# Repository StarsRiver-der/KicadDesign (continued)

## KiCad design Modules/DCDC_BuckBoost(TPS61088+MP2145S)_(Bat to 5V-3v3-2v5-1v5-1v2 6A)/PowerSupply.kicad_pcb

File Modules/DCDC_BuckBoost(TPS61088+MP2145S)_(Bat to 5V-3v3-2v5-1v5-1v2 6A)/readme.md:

# 2.8V-4.2V 锂电池输入的 DCDC 单极性多轨电源
* 工作温度：0-85℃
* 5V、3v3、2v5、1v5、1v2多轨输出
* 最高30W输出

# 注意事项
* 使用Kicad6绘制

# 原理
见说明手册

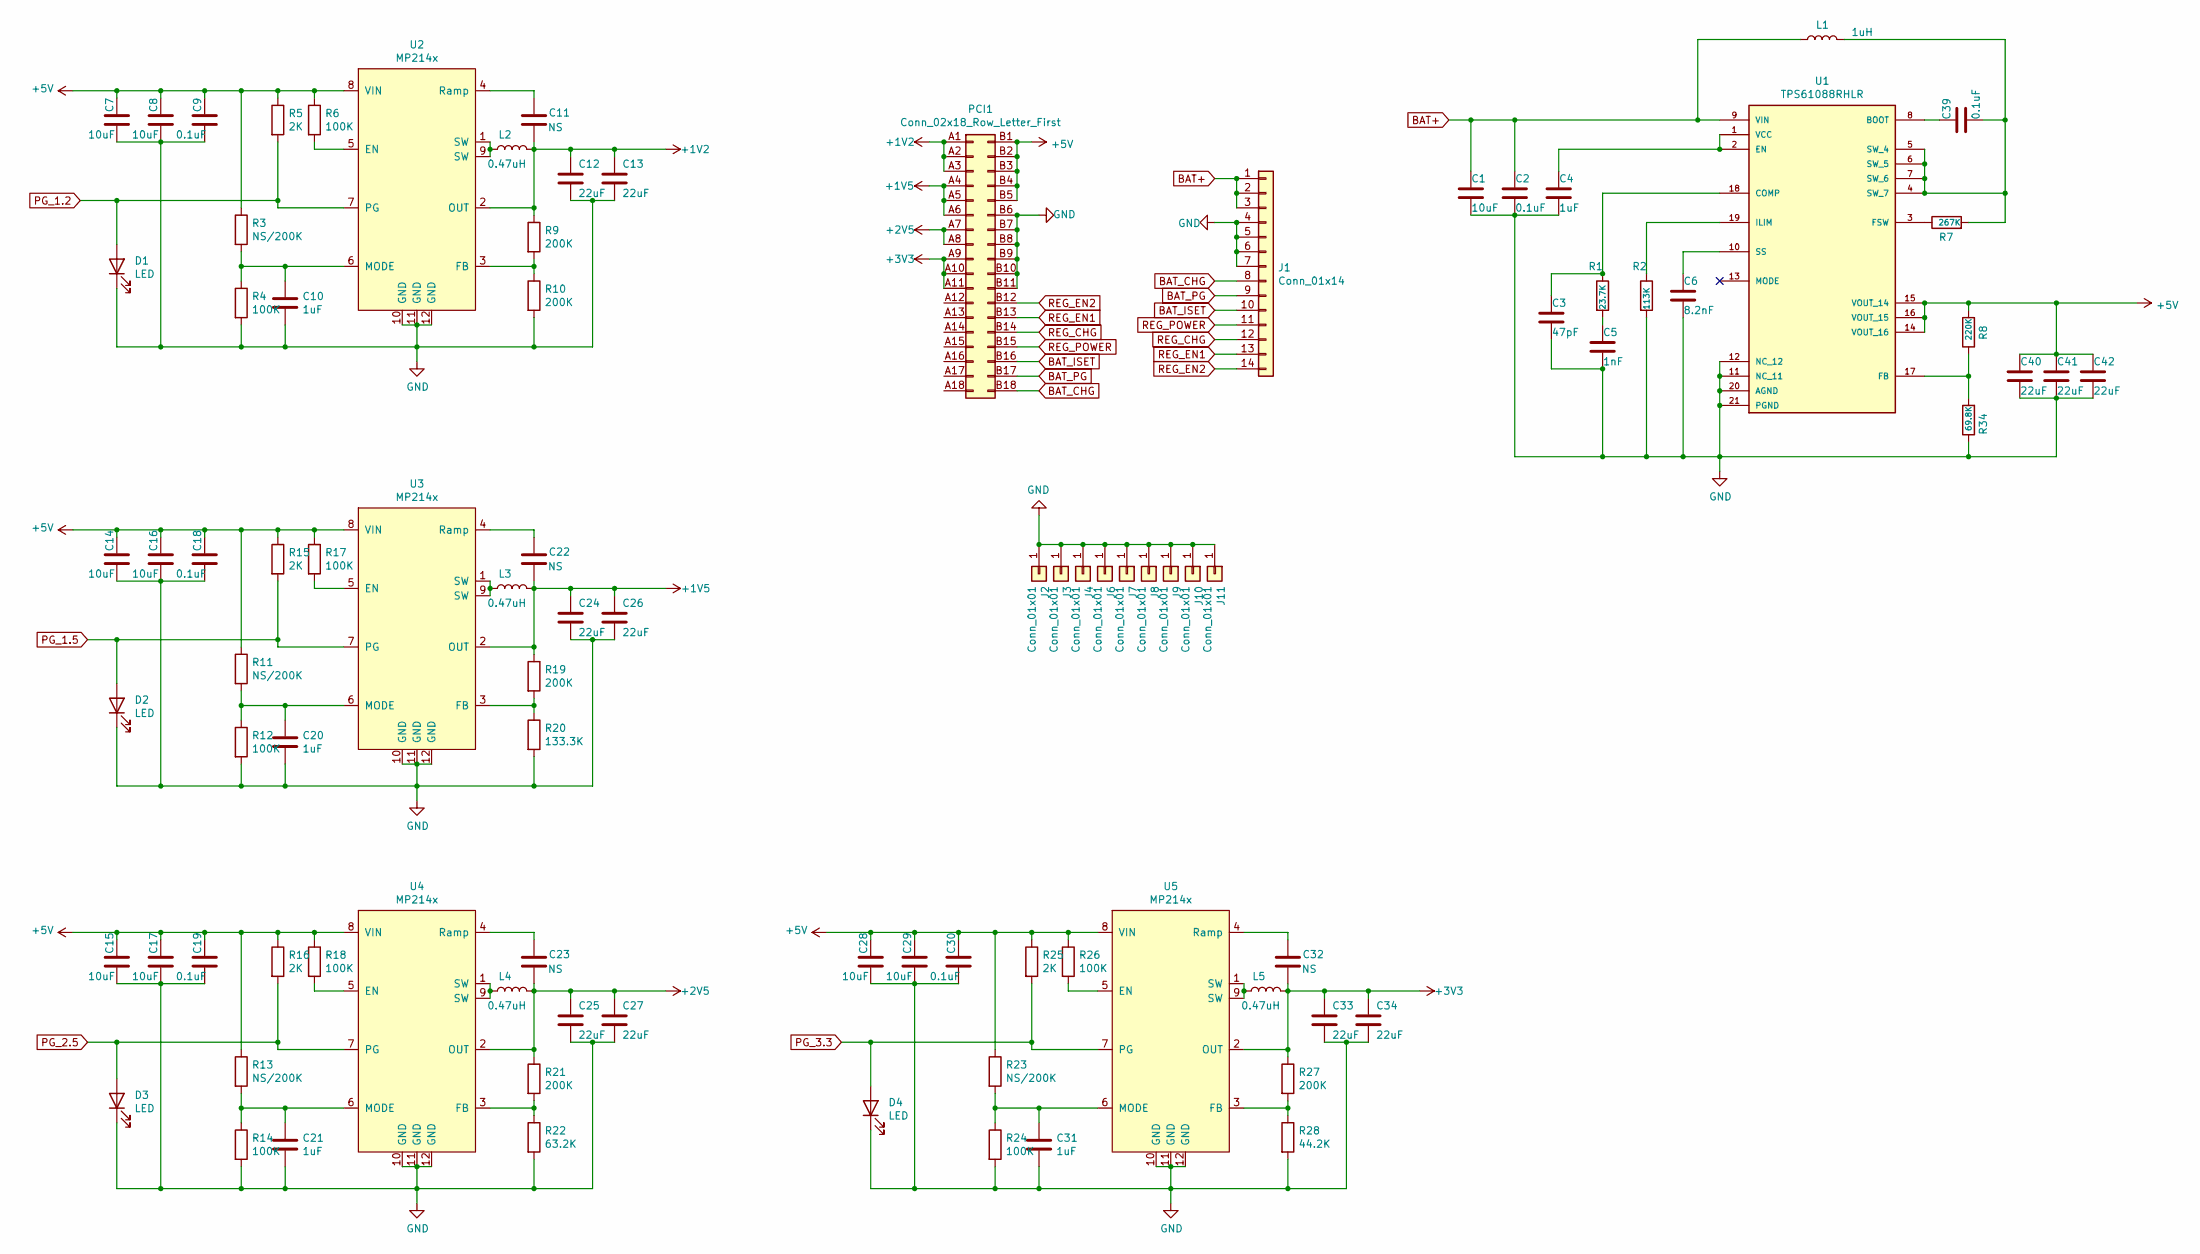
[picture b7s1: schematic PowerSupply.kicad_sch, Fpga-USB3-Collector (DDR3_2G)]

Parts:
C1, C7, C8, C14, C15, C16, C17, C28, C29: 10uF; C_0603_1608Metric
C2, C9, C18, C19, C30, C39: 0.1uF; C_0402_1005Metric
C3: 47pF; C_0402_1005Metric
C4, C10, C20, C21, C31: 1uF; C_0402_1005Metric
C5: 1nF; C_0402_1005Metric
C6: 8.2nF; C_0402_1005Metric
C11, C22, C23, C32: NS; C_0402_1005Metric
C12, C13, C24, C25, C26, C27, C33, C34, C40, C41, C42: 22uF; C_0603_1608Metric
D1, D2, D3, D4: LED; LED_0402_1005Metric
J1: Conn_01x14; Hirose_FH12-14S-0.5SH_1x14-1MP_P0.50mm_Horizontal
J2, J3, J4, J6, J7, J8, J9, J10, J11: Conn_01x01; pad-6-1.5
L1: 1uH; L_Sunlord_MWSA0518_5.4x5.2mm
L2, L3, L4, L5: 0.47uH; L_Sunlord_MWSA0518_5.4x5.2mm
PCI1: Conn_02x18_Row_Letter_First; BUS_PCIexpress_x1
R1: 23.7K; R_0402_1005Metric
R2: 113K; R_0402_1005Metric
R3, R11, R13, R23: NS/200K; R_0402_1005Metric
R4, R6, R12, R14, R17, R18, R24, R26: 100K; R_0402_1005Metric
R5, R15, R16, R25: 2K; R_0402_1005Metric
R7: 267K; R_0402_1005Metric
R8: 220K; R_0402_1005Metric
R9, R10, R19, R21, R27: 200K; R_0402_1005Metric
R20: 133.3K; R_0402_1005Metric
R22: 63.2K; R_0402_1005Metric
R28: 44.2K; R_0402_1005Metric
R34: 69.8K; R_0402_1005Metric
U1: TPS61088RHLR; IC_TPS61088RHLR; PARTREV 4219071/A 05/2017
U2, U3, U4, U5: MP214x; MP2145_2147_DG_Z

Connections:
+1V2: C11.1, C12.1, C13.1, L2.2, PCI1.A1, PCI1.A2, PCI1.A3, R9.1, U2.2 (OUT)
+1V5: C22.1, C24.1, C26.1, L3.2, PCI1.A4, PCI1.A5, PCI1.A6, R19.1, U3.2 (OUT)
+2V5: C23.1, C25.1, C27.1, L4.2, PCI1.A7, PCI1.A8, R21.1, U4.2 (OUT)
+3V3: C32.1, C33.1, C34.1, L5.2, PCI1.A9, PCI1.A10, PCI1.A11, R27.1, U5.2 (OUT)
+5V: C7.1, C8.1, C9.1, C14.1, C15.1, C16.1, C17.1, C18.1, C19.1, C28.1, C29.1, C30.1, C40.1, C41.1, C42.1, PCI1.B1, PCI1.B2, PCI1.B3, PCI1.B4, PCI1.B5, R3.1, R5.1, R6.1, R8.2, R11.1, R13.1, R15.1, R16.1, R17.1, R18.1, R23.1, R25.1, R26.1, U1.14 (VOUT_16), U1.15 (VOUT_14), U1.16 (VOUT_15), U2.8 (VIN), U3.8 (VIN), U4.8 (VIN), U5.8 (VIN)
BAT+: C1.1, C2.1, J1.1, J1.2, J1.3, L1.1, U1.9 (VIN)
BAT_CHG: J1.8, PCI1.B18
BAT_ISET: J1.10, PCI1.B16
BAT_PG: J1.9, PCI1.B17
GND: C1.2, C2.2, C3.2, C4.2, C5.2, C6.2, C7.2, C8.2, C9.2, C10.2, C12.2, C13.2, C14.2, C15.2, C16.2, C17.2, C18.2, C19.2, C20.2, C21.2, C24.2, C25.2, C26.2, C27.2, C28.2, C29.2, C30.2, C31.2, C33.2, C34.2, C40.2, C41.2, C42.2, D1.1 (K), D2.1 (K), D3.1 (K), D4.1 (K), J1.4, J1.5, J1.6, J1.7, J2.1, J3.1, J4.1, J6.1, J7.1, J8.1, J9.1, J10.1, J11.1, PCI1.B6, PCI1.B7, PCI1.B8, PCI1.B9, PCI1.B10, PCI1.B11, R2.2, R4.2, R10.2, R12.2, R14.2, R20.2, R22.2, R24.2, R28.2, R34.1, U1.11 (NC_11), U1.12 (NC_12), U1.20 (AGND), U1.21 (PGND), U2.10 (GND), U2.11 (GND), U2.12 (GND), U3.10 (GND), U3.11 (GND), U3.12 (GND), U4.10 (GND), U4.11 (GND), U4.12 (GND), U5.10 (GND), U5.11 (GND), U5.12 (GND)
unnamed: C3.1, R1.1, U1.18 (COMP)
unnamed: C4.1, U1.1 (VCC), U1.2 (EN)
unnamed: C5.1, R1.2
unnamed: C6.1, U1.10 (SS)
unnamed: C10.1, R3.2, R4.1, U2.6 (MODE)
unnamed: C11.2, U2.4 (Ramp)
unnamed: C20.1, R11.2, R12.1, U3.6 (MODE)
unnamed: C21.1, R13.2, R14.1, U4.6 (MODE)
unnamed: C22.2, U3.4 (Ramp)
unnamed: C23.2, U4.4 (Ramp)
unnamed: C31.1, R23.2, R24.1, U5.6 (MODE)
unnamed: C32.2, U5.4 (Ramp)
unnamed: C39.1, U1.8 (BOOT)
unnamed: C39.2, L1.2, R7.2, U1.4 (SW_7), U1.5 (SW_4), U1.6 (SW_5), U1.7 (SW_6)
unnamed: L2.1, U2.1 (SW), U2.9 (SW)
unnamed: L3.1, U3.1 (SW), U3.9 (SW)
unnamed: L4.1, U4.1 (SW), U4.9 (SW)
unnamed: L5.1, U5.1 (SW), U5.9 (SW)
unnamed: R2.1, U1.19 (ILIM)
unnamed: R6.2, U2.5 (EN)
unnamed: R7.1, U1.3 (FSW)
unnamed: R9.2, R10.1, U2.3 (FB)
unnamed: R17.2, U3.5 (EN)
unnamed: R18.2, U4.5 (EN)
unnamed: R19.2, R20.1, U3.3 (FB)
unnamed: R21.2, R22.1, U4.3 (FB)
unnamed: R26.2, U5.5 (EN)
unnamed: R27.2, R28.1, U5.3 (FB)
unnamed: R8.1, R34.2, U1.17 (FB)
PG_1.2: D1.2 (A), R5.2, U2.7 (PG)
PG_1.5: D2.2 (A), R15.2, U3.7 (PG)
PG_2.5: D3.2 (A), R16.2, U4.7 (PG)
PG_3.3: D4.2 (A), R25.2, U5.7 (PG)
REG_CHG: J1.12, PCI1.B14
REG_EN1: J1.13, PCI1.B13
REG_EN2: J1.14, PCI1.B12
REG_POWER: J1.11, PCI1.B15

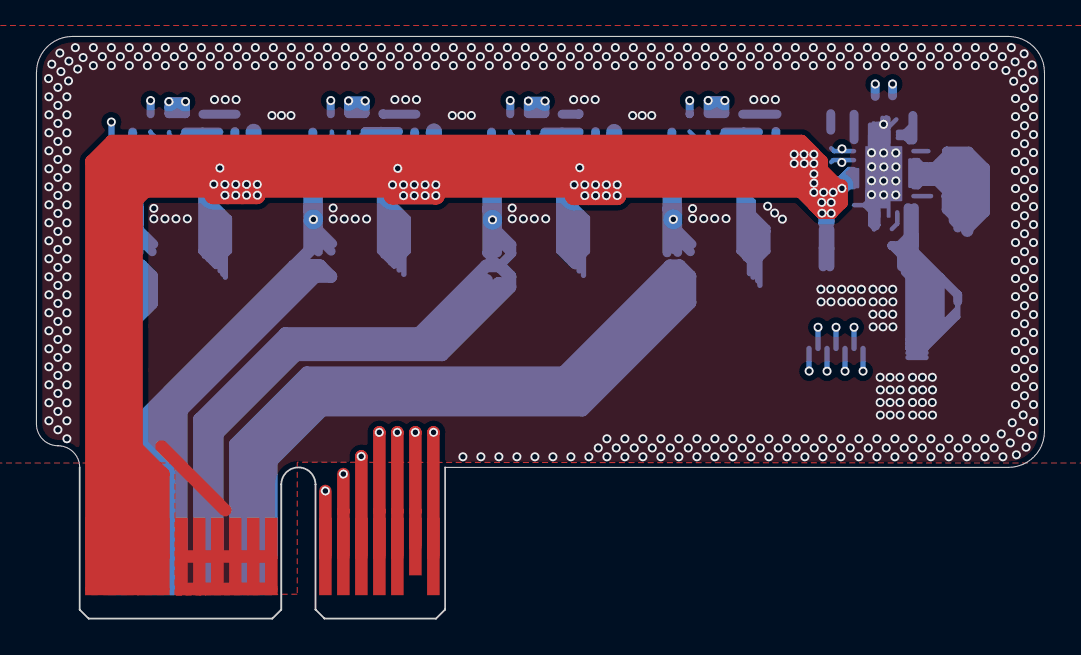
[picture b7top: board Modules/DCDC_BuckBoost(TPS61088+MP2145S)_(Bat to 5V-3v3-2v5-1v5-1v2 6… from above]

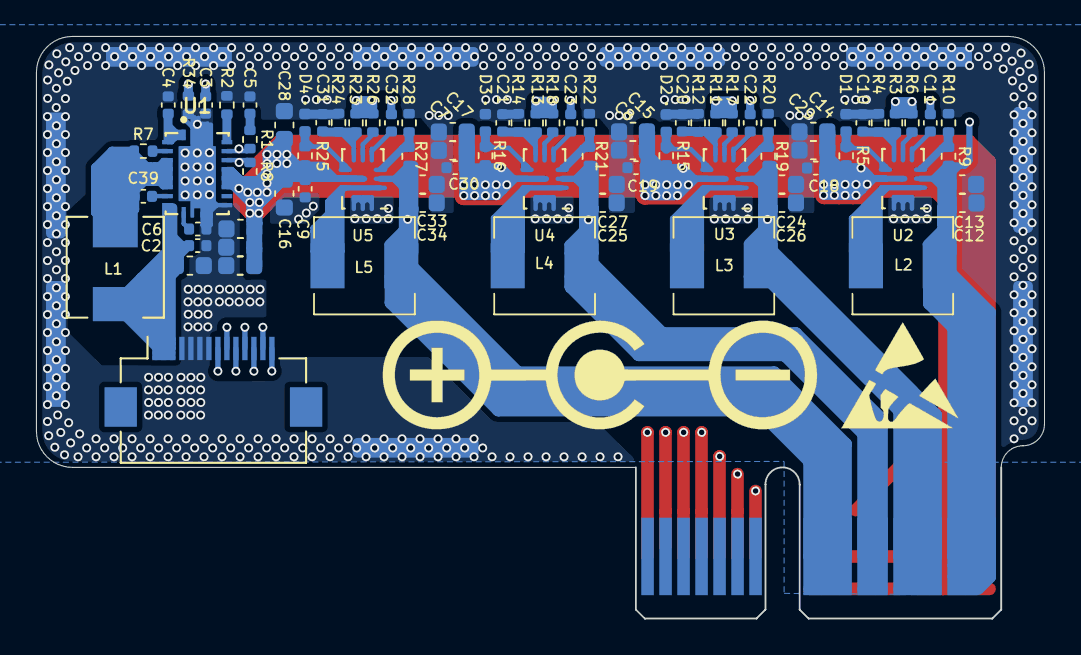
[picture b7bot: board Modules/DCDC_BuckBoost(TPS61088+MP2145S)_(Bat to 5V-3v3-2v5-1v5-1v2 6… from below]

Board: 4 copper layers, 56.0 x 32.3 mm, 92 parts (91 on the bottom side), 47 nets.
